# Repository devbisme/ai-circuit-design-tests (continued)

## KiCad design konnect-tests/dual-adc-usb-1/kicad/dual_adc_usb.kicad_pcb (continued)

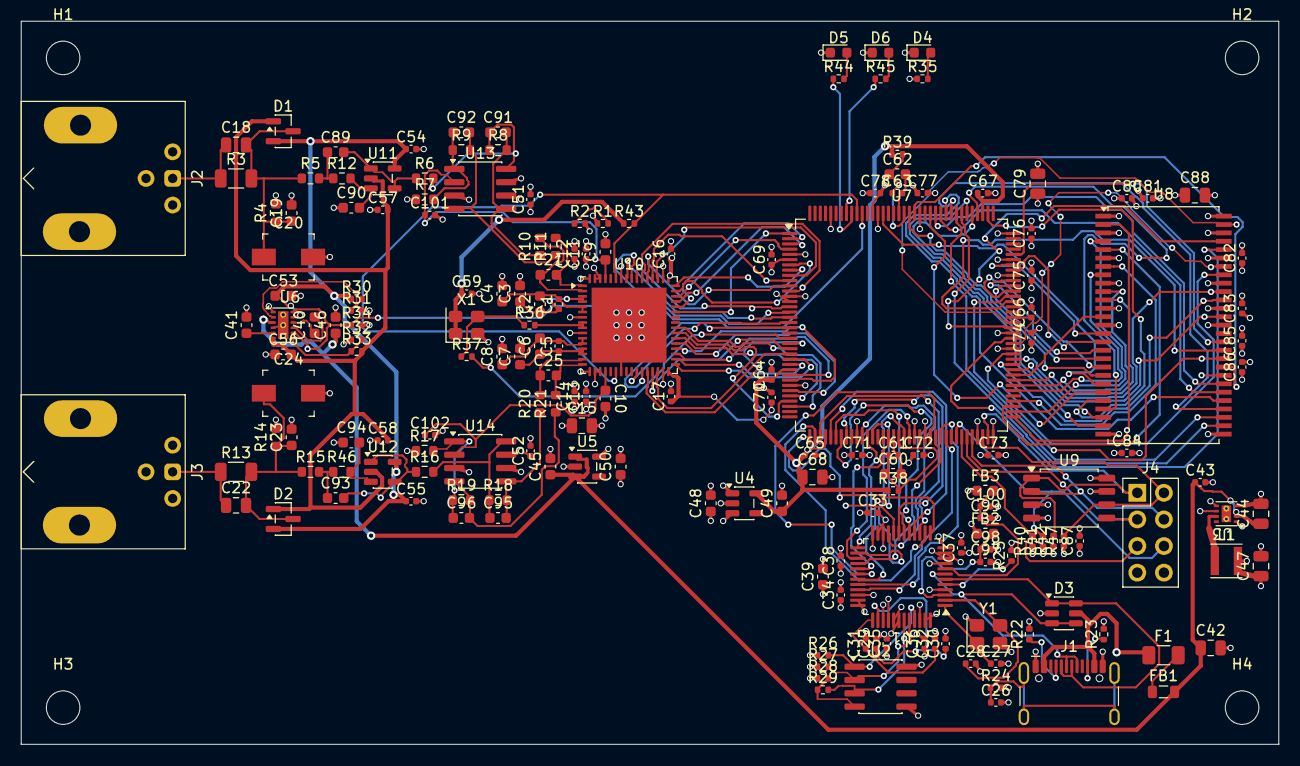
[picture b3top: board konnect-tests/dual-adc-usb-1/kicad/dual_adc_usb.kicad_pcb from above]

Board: 4 copper layers, 120.0 x 69.0 mm, 184 parts (0 on the bottom side), 163 nets.

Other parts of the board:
H1, H2, H3, H4: MountingHole_3.2mm_M3

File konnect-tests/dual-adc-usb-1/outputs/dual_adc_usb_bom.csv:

"Reference","Value","Footprint","Tolerance","Voltage","Dielectric","QUANTITY"
"C1,C5,C11-C14,C16,C17,C29-C38,C43,C51,C52,C54,C55,C57-C59,C61,C63-C67,C69-C78,C80-C87,C98,C100","100nF","Capacitor_SMD:C_0402_1005Metric","","","","52"
"C2,C6,C9,C10,C46,C53,C56","2.2uF","Capacitor_SMD:C_0603_1608Metric","","","","7"
"C3,C4,C7,C8,C40,C45,C48-C50","1uF","Capacitor_SMD:C_0603_1608Metric","","","","9"
"C15,C42,C44,C68,C79,C88","10uF","Capacitor_SMD:C_0805_2012Metric","","","","6"
"C18,C22","12pF","Capacitor_SMD:C_0805_2012Metric","","100V","C0G","2"
"C19,C23","180pF","Capacitor_SMD:C_0603_1608Metric","","","C0G","2"
"C20,C24","5-30pF","Capacitor_SMD:C_Trimmer_Murata_TZB4-A","","","","2"
"C21,C25","100pF","Capacitor_SMD:C_0603_1608Metric","","","C0G","2"
"C26","4.7nF","Capacitor_SMD:C_0402_1005Metric","","","","1"
"C27,C28","27pF","Capacitor_SMD:C_0402_1005Metric","","","","2"
"C39,C41,C60,C62","4.7uF","Capacitor_SMD:C_0603_1608Metric","","","","4"
"C47","22uF","Capacitor_SMD:C_0805_2012Metric","","","","1"
"C89,C93","150pF","Capacitor_SMD:C_0603_1608Metric","","","C0G","2"
"C90,C94","39pF","Capacitor_SMD:C_0603_1608Metric","","","C0G","2"
"C91,C92,C95,C96","82pF","Capacitor_SMD:C_0603_1608Metric","","","C0G","4"
"C97,C99","10nF","Capacitor_SMD:C_0402_1005Metric","","","","2"
"C101,C102","220nF","Capacitor_SMD:C_0402_1005Metric","","","","2"
"D1,D2","BAV99","Package_TO_SOT_SMD:SOT-23","","","","2"
"D3","USBLC6-2SC6","Package_TO_SOT_SMD:SOT-23-6","","","","1"
"D4","PWR (green)","LED_SMD:LED_0603_1608Metric","","","","1"
"D5","LED0 (red)","LED_SMD:LED_0603_1608Metric","","","","1"
"D6","LED1 (red)","LED_SMD:LED_0603_1608Metric","","","","1"
"F1","0.75A","Fuse:Fuse_1206_3216Metric","","","","1"
"FB1","600R 2A","Inductor_SMD:L_0805_2012Metric","","","","1"
"FB2,FB3","600R","Inductor_SMD:L_0603_1608Metric","","","","2"
"J1","USB_C_Receptacle_USB2.0_16P","Connector_USB:USB_C_Receptacle_GCT_USB4105-xx-A_16P_TopMnt_Horizontal","","","","1"
"J2","BNC CHA","Connector_Coaxial:BNC_Amphenol_031-6575_Horizontal","","","","1"
"J3","BNC CHB","Connector_Coaxial:BNC_Amphenol_031-6575_Horizontal","","","","1"
"J4","iCE40 prog","Connector_PinHeader_2.54mm:PinHeader_2x04_P2.54mm_Vertical","","","","1"
"L1","2.2uH","Inductor_SMD:L_Taiyo-Yuden_NR-30xx","","","","1"
"R1,R26-R28,R40-R43,R47","10k","Resistor_SMD:R_0402_1005Metric","","","","9"
"R2","20k","Resistor_SMD:R_0402_1005Metric","","","","1"
"R3,R13","953k","Resistor_SMD:R_1206_3216Metric","0.1%","200V","","2"
"R4,R14","47.5k","Resistor_SMD:R_0603_1608Metric","0.1%","","","2"
"R5,R8,R9,R12,R15,R18,R19,R46","1k","Resistor_SMD:R_0603_1608Metric","0.1%","","","8"
"R6,R7,R16,R17","499","Resistor_SMD:R_0603_1608Metric","0.1%","","","4"
"R10,R11,R20,R21","49.9","Resistor_SMD:R_0603_1608Metric","","","","4"
"R22,R23","5.1k","Resistor_SMD:R_0402_1005Metric","","","","2"
"R24","1M","Resistor_SMD:R_0402_1005Metric","","","","1"
"R25","12k","Resistor_SMD:R_0402_1005Metric","1%","","","1"
"R29","2.2k","Resistor_SMD:R_0402_1005Metric","","","","1"
"R30","107k","Resistor_SMD:R_0402_1005Metric","1%","","","1"
"R31,R32","100k","Resistor_SMD:R_0402_1005Metric","1%","","","2"
"R33","105k","Resistor_SMD:R_0402_1005Metric","1%","","","1"
"R34","100k","Resistor_SMD:R_0402_1005Metric","","","","1"
"R35","1k","Resistor_SMD:R_0402_1005Metric","","","","1"
"R36,R37","33","Resistor_SMD:R_0402_1005Metric","","","","2"
"R38,R39","100","Resistor_SMD:R_0402_1005Metric","","","","2"
"R44,R45","330","Resistor_SMD:R_0402_1005Metric","","","","2"
"U1","FT232HL","Package_QFP:LQFP-48_7x7mm_P0.5mm","","","","1"
"U2","93LC56B","Package_SO:SOIC-8_3.9x4.9mm_P1.27mm","","","","1"
"U3","TPS62162DSG","Package_SON:WSON-8-1EP_2x2mm_P0.5mm_EP0.9x1.6mm_ThermalVias","","","","1"
"U4","TLV75512PDBV","Package_TO_SOT_SMD:SOT-23-5","","","","1"
"U5","LP5907MFX-3.3","Package_TO_SOT_SMD:SOT-23-5","","","","1"
"U6","LM27762","Package_SON:WSON-12-1EP_3x2mm_P0.5mm_EP1x2.65_ThermalVias","","","","1"
"U7","ICE40HX4K-TQ144","Package_QFP:TQFP-144_20x20mm_P0.5mm","","","","1"
"U8","MT48LC16M16A2TG","Package_SO:TSOP-II-54_22.2x10.16mm_P0.8mm","","","","1"
"U9","W25Q32JVSS","Package_SO:SOIC-8_5.3x5.3mm_P1.27mm","","","","1"
"U10","LTC2290xUP","Package_DFN_QFN:QFN-64-1EP_9x9mm_P0.5mm_EP7.15x7.15mm","","","","1"
"U11,U12","OPA356","Package_TO_SOT_SMD:SOT-23-5","","","","2"
"U13,U14","THS4521ID","Package_SO:SOIC-8_3.9x4.9mm_P1.27mm","","","","2"
"X1","ASE-10.000MHz-LC-T","Oscillator:Oscillator_SMD_Abracon_ASE-4Pin_3.2x2.5mm","","","","1"
"Y1","12MHz","Crystal:Crystal_SMD_3225-4Pin_3.2x2.5mm","","","","1"
